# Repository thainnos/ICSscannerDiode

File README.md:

# A Secure Network Scanner Architecture for Asset Management in Strongly Segmented ICS Networks

<table align="center"><tr><td align="center" width="9999">
</img>
</td></tr></table>

This GIT provides all necessary material to setup the network scanner for industrial networks.
The network scanner is based on a strict segmentation between the OT and IT network.
For this two Raspberry Pis, one in the IT network and the other in the OT network are used.
These are communicating over a SPI bus with each other, where a microcontroller is placed in acting
as a data filter/diode.

## Prototype
All this is implemented on a central PCB, where all parts get attached to.
The image below shows the PCB of the network scanner.

<table align="center"><tr><td align="center" width="9999">
</img>
</td></tr></table>

A fully assebled network scanner, with the two Raspberry Pis and OLED displays is illustraed below.

<table align="center"><tr><td align="center" width="9999">
</img>
</td></tr></table>

## Scan control and results (Web frontend)

The scan can be started and stopped over the web frontend.
<table align="center"><tr><td align="center" width="9999">
</img>
</td></tr></table>

The results are shown in a table.
<table align="center"><tr><td align="center" width="9999">
</img>
</td></tr></table>

## Content
* [Software](software/README.md)
* [Hardware](hardware/README.md)
* [Images](images/README.md)

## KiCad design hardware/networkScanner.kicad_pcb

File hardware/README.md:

# Hardware of the Secure ICS Network Scanner

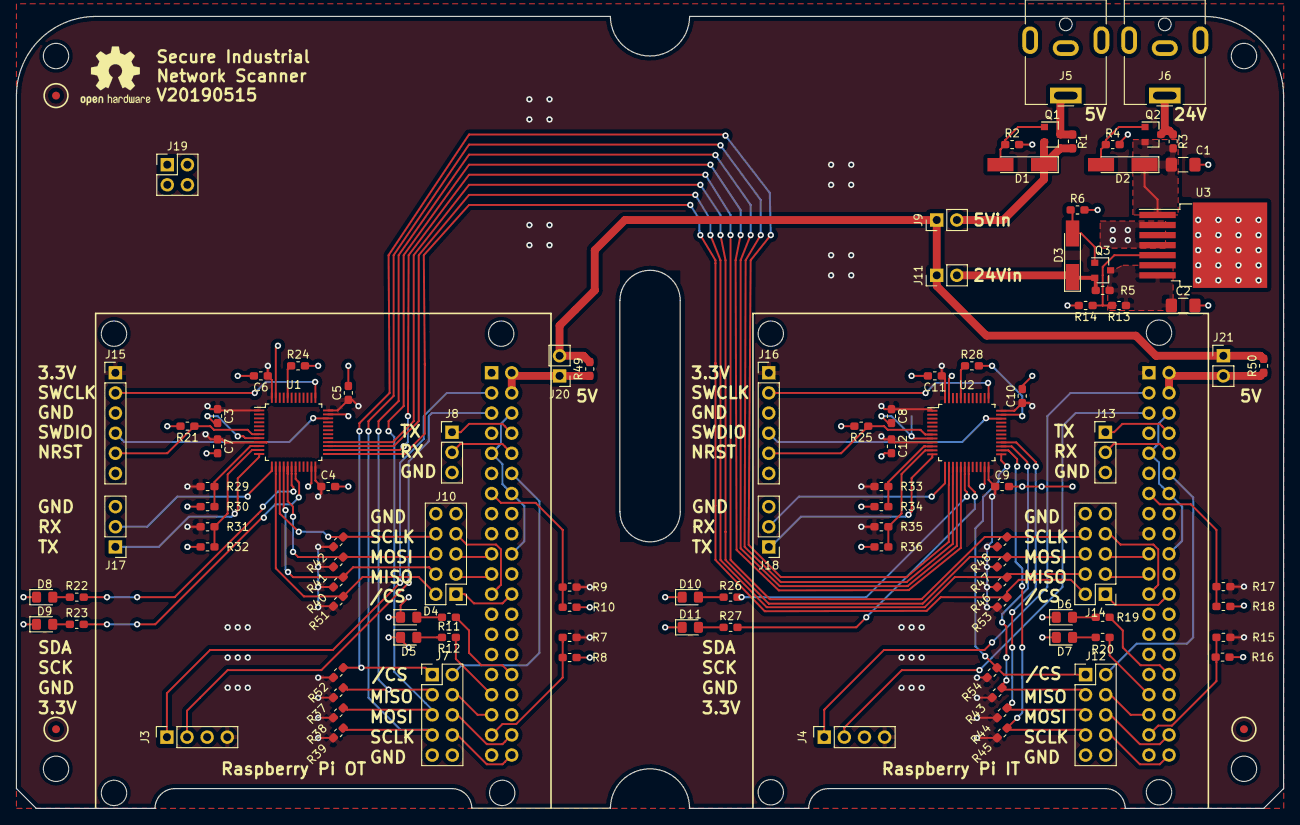
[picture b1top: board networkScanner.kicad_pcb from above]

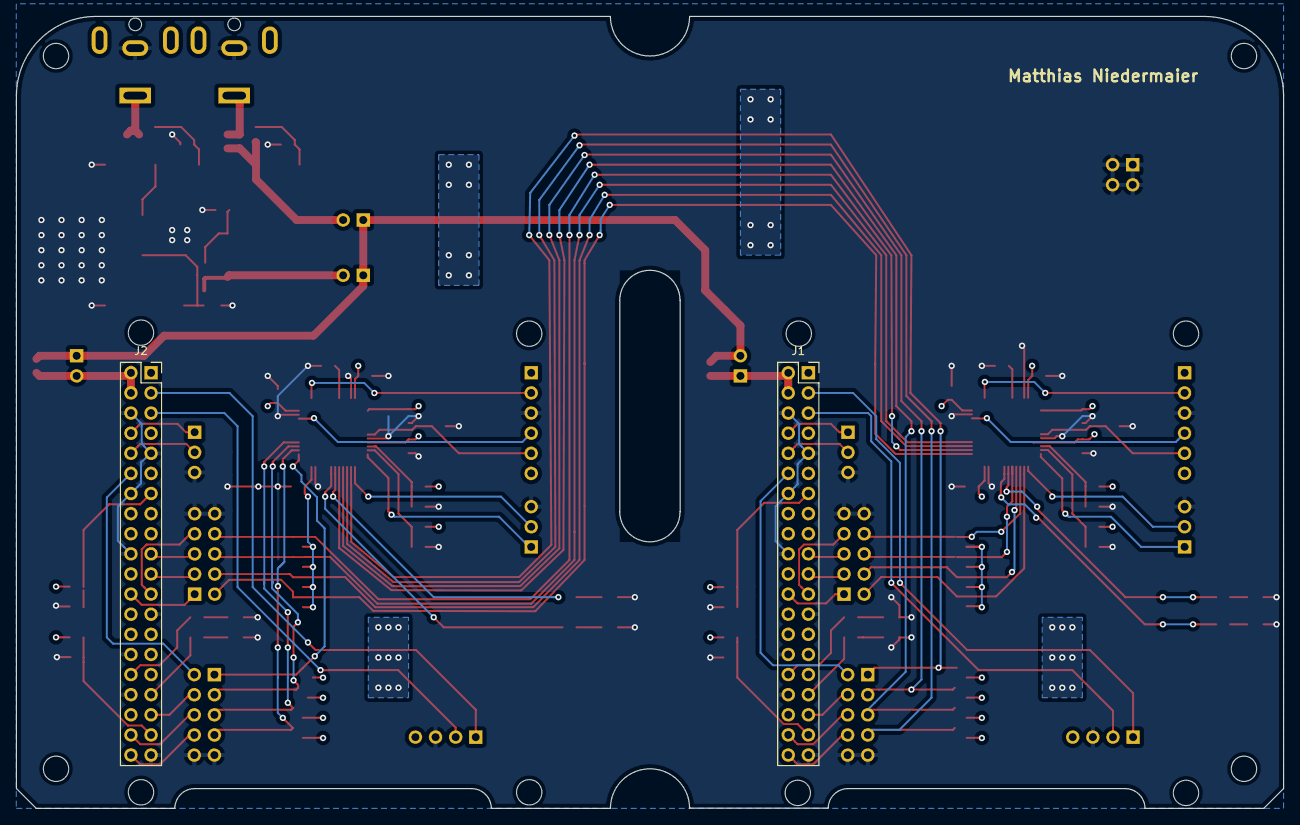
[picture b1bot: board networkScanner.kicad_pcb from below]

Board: 2 copper layers, 160.0 x 100.0 mm, 104 parts (2 on the bottom side), 91 nets.

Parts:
C1, C2: 22µF; C_1206_3216Metric_Pad1.42x1.75mm_HandSolder
C3, C4, C5, C6, C7, C8, C9, C10, C11, C12: 100nF; C_0603_1608Metric_Pad1.05x0.95mm_HandSolder
D1: ZPDxx; D_MiniMELF_Handsoldering
D2, D3: ZPD15; D_MiniMELF_Handsoldering
D4, D5, D6, D7, D8, D9, D10, D11: LED; LED_0805_2012Metric_Pad1.15x1.40mm_HandSolder
J1, J2: Raspberry_Pi_2_3; PinSocket_2x20_P2.54mm_Vertical
J3, J4: Conn_01x04_Female; PinSocket_1x04_P2.54mm_Vertical
J5, J6: Jack-DC; BarrelJack_CUI_PJ-063AH_Horizontal
J7, J10, J12, J14: Conn_02x05_Odd_Even; PinHeader_2x05_P2.54mm_Vertical
J8, J13, J17, J18: Conn_01x03_Male; PinHeader_1x03_P2.54mm_Vertical
J9, J11, J20, J21: Conn_01x02_Male; PinHeader_1x02_P2.54mm_Vertical
J15, J16: Conn_01x06_Male; PinHeader_1x06_P2.54mm_Vertical
J19: Conn_02x02_Odd_Even; PinHeader_2x02_P2.54mm_Vertical
Q1, Q2, Q3: BSS84; SOT-23
R1, R3, R5, R49, R50: 0R; R_0603_1608Metric_Pad1.05x0.95mm_HandSolder
R2, R4, R6: 100kR; R_0603_1608Metric_Pad1.05x0.95mm_HandSolder
R7, R8, R9, R10, R15, R16, R17, R18, R21, R24, R25, R28, R29, R30, R31, R32, R33, R34, R35, R36, R37, R38, R39, R40, R41, R42, R43, R44, R45, R46, R47, R48, R51, R52, R53, R54: 10kR; R_0603_1608Metric_Pad1.05x0.95mm_HandSolder
R11, R12, R19, R20, R22, R23, R26, R27: 330R; R_0603_1608Metric_Pad1.05x0.95mm_HandSolder
R13: 5.62kR; R_0603_1608Metric_Pad1.05x0.95mm_HandSolder
R14: 1.07kR; R_0603_1608Metric_Pad1.05x0.95mm_HandSolder
U1, U2: STM32F030CCTx; LQFP-48_7x7mm_P0.5mm
U3: LMZ23605; TO-263-7_TabPin4

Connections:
+3V3: C3.1, C4.1, C5.1, C6.1, C7.1, C8.1, C9.1, C10.1, C11.1, C12.1, J2.1, J2.17, J3.4, J4.4, J15.1, J16.1, R7.2, R9.2, R15.2, R17.2, R29.1, R31.1, R33.1, R35.1, R37.1, R38.1, R39.1, R40.1, R41.1, R42.1, R43.1, R44.1, R45.1, R46.1, R47.1, R48.1, R51.1, R52.1, R53.1, R54.1, U1.1, U1.9, U1.24, U1.36, U1.48, U2.1, U2.9, U2.24, U2.36, U2.48
+5V: J9.1, J11.1, J20.2, J21.1, R49.2, R50.2
+24V: C1.1, D2.1, Q2.2, R3.1, U3.1
/Sheet5CCB0C0B/NRST1: J15.5, R21.1, U1.7
/Sheet5CCB0C0B/NRST2: J16.5, R25.1, U2.7
/Sheet5CCB0C0B/SWCLK1: J15.2, U1.37
/Sheet5CCB0C0B/SWCLK2: J16.2, U2.37
/Sheet5CCB0C0B/SWDIO1: J15.4, U1.34
/Sheet5CCB0C0B/SWDIO2: J16.4, U2.34
GND: C1.2, C2.2, C3.2, C4.2, C5.2, C6.2, C7.2, C8.2, C9.2, C10.2, C11.2, C12.2, D4.1, D5.1, D6.1, D7.1, D8.1, D9.1, D10.1, D11.1, J1.6, J1.9, J1.14, J1.20, J1.25, J1.30, J1.34, J1.39, J2.6, J2.9, J2.14, J2.20, J2.25, J2.30, J2.34, J2.39, J3.3, J4.3, J5.2, J6.2, J7.9, J7.10, J8.3, J10.9, J10.10, J12.9, J12.10, J13.3, J14.9, J14.10, J15.3, J16.3, J17.3, J18.3, J19.1, J19.2, J19.3, J19.4, R2.2, R4.2, R6.2, R8.2, R10.2, R14.2, R16.2, R18.2, R21.2, R24.2, R25.2, R28.2, R30.1, R32.1, R34.1, R36.1, U1.8, U1.23, U1.35, U1.47, U2.8, U2.23, U2.35, U2.47, U3.2, U3.4
unnamed: C2.1, Q3.3, R5.2, R13.1, U3.7
unnamed: D1.1, J9.2, Q1.2, R1.1
unnamed: D1.2, Q1.1, R2.1
unnamed: D2.2, Q2.1, R4.1
unnamed: D3.1, J11.2, Q3.2, R5.1
unnamed: D3.2, Q3.1, R6.1
unnamed: D4.2, R11.1
unnamed: D5.2, R12.1
unnamed: D6.2, R19.1
unnamed: D7.2, R20.1
unnamed: D8.2, R22.1
unnamed: D9.2, R23.1
unnamed: D10.2, R26.1
unnamed: D11.2, R27.1
unnamed: J1.2, J1.4, J20.1, R49.1
unnamed: J1.3, J3.1
unnamed: J1.5, J3.2
unnamed: J1.8, J8.1
unnamed: J1.10, J8.2
unnamed: J1.12, J7.2
unnamed: J1.13, R9.1, R10.1
unnamed: J1.19, J10.5
unnamed: J1.21, J10.3
unnamed: J1.23, J10.7
unnamed: J1.24, J10.1
unnamed: J1.32, R11.2
unnamed: J1.33, R12.2
unnamed: J1.35, J7.4
unnamed: J1.37, R7.1, R8.1
unnamed: J1.38, J7.6
unnamed: J1.40, J7.8
unnamed: J2.2, J2.4, J21.2, R50.1
unnamed: J2.3, J4.1
unnamed: J2.5, J4.2
unnamed: J2.13, R17.1, R18.1
unnamed: J2.32, R19.2
unnamed: J2.33, R20.2
unnamed: J2.37, R15.1, R16.1
unnamed: J5.1, Q1.3, R1.2
unnamed: J6.1, Q2.3, R3.2
unnamed: J2.12, J12.2
unnamed: J2.35, J12.4
unnamed: J2.38, J12.6
unnamed: J2.40, J12.8
unnamed: J2.8, J13.1
unnamed: J2.10, J13.2
unnamed: J2.24, J14.1
unnamed: J2.21, J14.3
unnamed: J2.19, J14.5
unnamed: J2.23, J14.7
unnamed: J17.1, U1.12
unnamed: J17.2, U1.13
unnamed: J18.1, U2.12
unnamed: J18.2, U2.13
unnamed: R13.2, R14.1, U3.5
unnamed: R22.2, U1.18
unnamed: R23.2, U1.19
unnamed: R24.1, U1.44
unnamed: R26.2, U2.18
unnamed: R27.2, U2.19
unnamed: R28.1, U2.44
unnamed: R29.2, R30.2, U1.10
unnamed: R31.2, R32.2, U1.11
unnamed: R33.2, R34.2, U2.10
unnamed: R35.2, R36.2, U2.11
RP1-CS0: J10.2, R51.2, U1.14
RP1-CS1: J7.1, R52.2, U2.14
RP1-MISO0: J10.4, R40.2, U1.16
RP1-MISO1: J7.3, R37.2, U2.16
RP1-MOSI0: J10.6, R41.2, U1.17
RP1-MOSI1: J7.5, R38.2, U2.17
RP1-SCLK0: J10.8, R42.2, U1.15
RP1-SCLK1: J7.7, R39.2, U2.15
RP2-CS0: J14.2, R53.2, U1.25
RP2-CS1: J12.1, R54.2, U2.25
RP2-MISO0: J14.4, R46.2, U1.27
RP2-MISO1: J12.3, R43.2, U2.27
RP2-MOSI0: J14.6, R47.2, U1.28
RP2-MOSI1: J12.5, R44.2, U2.28
RP2-SCLK0: J14.8, R48.2, U1.26
RP2-SCLK1: J12.7, R45.2, U2.26

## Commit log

2020-11-21 flawfinder report added
